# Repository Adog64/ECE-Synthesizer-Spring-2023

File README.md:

# ECE-Synthesizer-Spring-2023

Our project consists of a synthesizer that plays notes from C4 to B5 using buttons. The MSP430 provides square, triangle, and sawtooth waves. The audio will be comprised of a combination of these waves, which can be altered. The volume will be adjustable.

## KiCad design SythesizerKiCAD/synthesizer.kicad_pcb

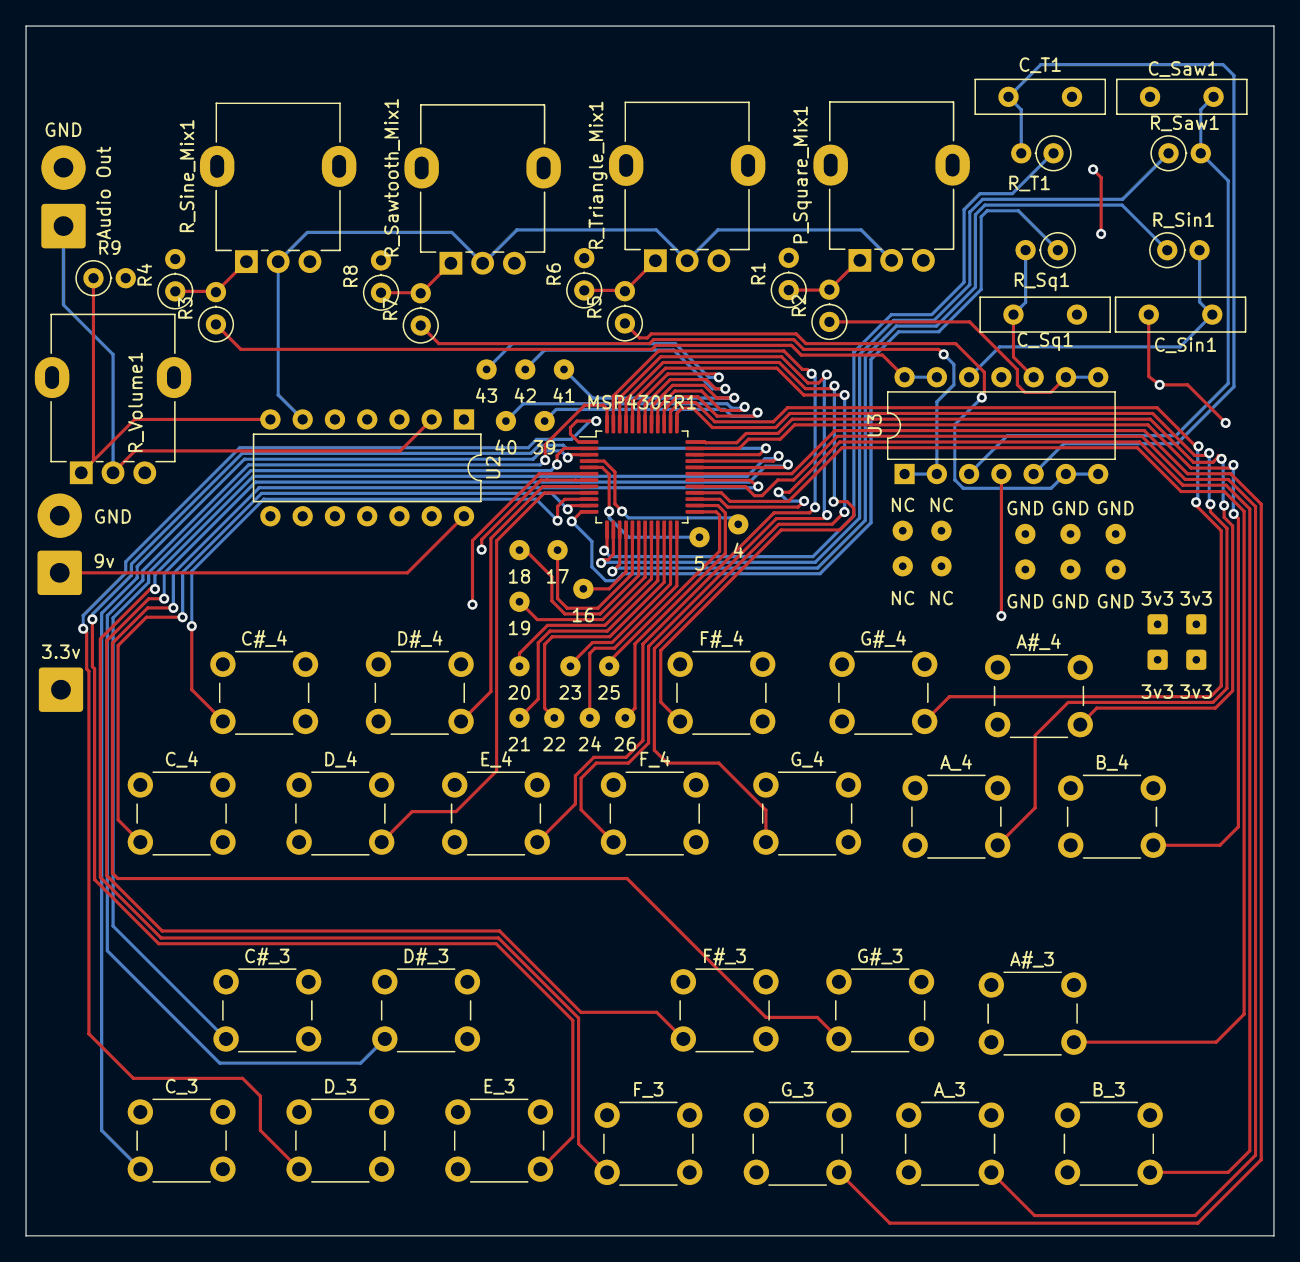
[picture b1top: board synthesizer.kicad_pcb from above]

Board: 2 copper layers, 98.2 x 95.2 mm, 86 parts (0 on the bottom side), 48 nets.

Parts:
3.3v, 9v: SolderWire-0.75sqmm_1x01_D1.25mm_OD3.5mm
3v3, 3v3#2, 3v3#3, 3v3#4, 4, 5, 16, 17, 18, 19, 20, 21, 22, 23, 24, 25, 26, 39, 40, 41, 42, 43: SolderWire-0.1sqmm_1x01_D0.4mm_OD1mm
A#_3, A#_4: SW_Push; SW_PUSH_6mm_H5mm
A_3, A_4: SW_Push; SW_PUSH_6mm_H5mm
Audio Out: SolderWire-0.75sqmm_1x01_D1.25mm_OD3.5mm
B_3, B_4: SW_Push; SW_PUSH_6mm_H5mm
C#_3, C#_4: SW_Push; SW_PUSH_6mm_H5mm
C_3, C_4: SW_Push; SW_PUSH_6mm_H5mm
C_Saw1: 1nF; C_Disc_D10.0mm_W2.5mm_P5.00mm
C_Sin1: 1nF; C_Disc_D10.0mm_W2.5mm_P5.00mm
C_Sq1: 1nF; C_Disc_D10.0mm_W2.5mm_P5.00mm
C_T1: 1nF; C_Disc_D10.0mm_W2.5mm_P5.00mm
D#_3, D#_4: SW_Push; SW_PUSH_6mm_H5mm
D_3, D_4: SW_Push; SW_PUSH_6mm_H5mm
E_3, E_4: SW_Push; SW_PUSH_6mm_H5mm
F#_3, F#_4: SW_Push; SW_PUSH_6mm_H5mm
F_3, F_4: SW_Push; SW_PUSH_6mm_H5mm
G#_3, G#_4: SW_Push; SW_PUSH_6mm_H5mm
GND: SolderWire-0.1sqmm_1x01_D0.4mm_OD1mm
GND#2, GND#3, GND#4, GND#6, GND#8: SolderWire-0.1sqmm_1x01_D0.4mm_OD1mm
GND#5, GND#7: SolderWire-0.75sqmm_1x01_D1.25mm_OD3.5mm
G_3, G_4: SW_Push; SW_PUSH_6mm_H5mm
MSP430FR1: LQFP-48_7x7mm_P0.5mm
NC: SolderWire-0.1sqmm_1x01_D0.4mm_OD1mm
NC#2, NC#3, NC#4: SolderWire-0.1sqmm_1x01_D0.4mm_OD1mm
P_Square_Mix1: R_Potentiometer_US; Potentiometer_Alpha_RD901F-40-00D_Single_Vertical
R1, R4, R6, R8, R9: 100k; R_Axial_DIN0207_L6.3mm_D2.5mm_P2.54mm_Vertical
R2, R3, R5, R7: 300k; R_Axial_DIN0207_L6.3mm_D2.5mm_P2.54mm_Vertical
R_Saw1: 8.2k; R_Axial_DIN0207_L6.3mm_D2.5mm_P2.54mm_Vertical
R_Sawtooth_Mix1: R_Potentiometer_US; Potentiometer_Alpha_RD901F-40-00D_Single_Vertical
R_Sin1: 8.2k; R_Axial_DIN0207_L6.3mm_D2.5mm_P2.54mm_Vertical
R_Sine_Mix1: R_Potentiometer_US; Potentiometer_Alpha_RD901F-40-00D_Single_Vertical
R_Sq1: 8.2k; R_Axial_DIN0207_L6.3mm_D2.5mm_P2.54mm_Vertical
R_T1: 8.2k; R_Axial_DIN0207_L6.3mm_D2.5mm_P2.54mm_Vertical
R_Triangle_Mix1: R_Potentiometer_US; Potentiometer_Alpha_RD901F-40-00D_Single_Vertical
R_Volume1: R_Potentiometer_US; Potentiometer_Alpha_RD901F-40-00D_Single_Vertical
U2: LM1877; DIP-14_W7.62mm
U3: LMC6484; DIP-14_W7.62mm

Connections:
/3v3: 3.3v.1, 3v3.1, 3v3#2.1, 3v3#3.1, 3v3#4.1, A#_3.1, A#_4.1, A_3.1, A_4.1, B_3.1, B_4.1, C#_3.1, C#_4.1, C_3.1, C_4.1, D#_3.1, D#_4.1, D_3.1, D_4.1, E_3.1, E_4.1, F#_3.1, F#_4.1, F_3.1, F_4.1, G#_3.1, G#_4.1, G_3.1, G_4.1, MSP430FR1.6 (DVCC), U3.4 (V+)
/9v: 9v.1, U2.14 (V+)
/Audio_Out: Audio Out.1, GND#5.1, R_Volume1.2, U2.2
/GND: C_Saw1.2, C_Sin1.2, C_Sq1.2, C_T1.2, GND.1, GND#2.1, GND#3.1, GND#4.1, GND#6.1, GND#7.1, GND#8.1, MSP430FR1.7 (DVSS), P_Square_Mix1.3, R1.2, R4.2, R6.2, R8.2, R9.2, R_Sawtooth_Mix1.3, R_Sine_Mix1.3, R_Triangle_Mix1.3, U2.3 (GND), U2.4 (GND), U2.5 (GND), U2.10 (GND), U2.11 (GND), U2.12 (GND), U3.11 (V-)
/Mixed: P_Square_Mix1.2, R_Sawtooth_Mix1.2, R_Sine_Mix1.2, R_Triangle_Mix1.2, U2.6 (+)
/P1.0: C_3.2, MSP430FR1.3 (P1.0/UCB0STE/SMCLK/COMP0.0/A0/Veref+)
/P1.1: C#_3.2, MSP430FR1.2 (P1.1/UCB0CLK/ACLK/OA0O/COMP0.1/A1)
/P1.2: D_3.2, MSP430FR1.1 (P1.2/UCB0SIMO/UCB0SDA/TB0TRG/OA0-/A2/Ve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)
/P1.3: D#_3.2, MSP430FR1.48 (1.3/UCB0SOMI/UCB0SCL/A3)
/P1.4: E_3.2, MSP430FR1.34 (P1.4/UCA0STE/TCK/A4)
/P1.5: F_3.2, MSP430FR1.33 (P1.5/UCA0CLK/TMS/A5)
/P1.6: F#_3.2, MSP430FR1.32 (P1.6/UCA0RXD/UCA0SOMI/TB0.1/TDI/TCLK/A6)
/P1.7: G_3.2, MSP430FR1.31 (P1.7/UCA0TXD/UCA0SIMO/TB0.2/TDO/A7/VREF+)
/P2.0: G#_3.2, MSP430FR1.30 (P2.0/TB1.1/COMP0.O)
/P2.1: A_3.2, MSP430FR1.29 (P2.1/TB1.2/COMP1.O)
/P2.2: A#_3.2, MSP430FR1.28 (P2.2/TB1CLK)
/P2.3: B_3.2, MSP430FR1.27 (P2.3/TB1TRG)
/P2.4: C_4.2, MSP430FR1.11 (P2.4/COMP1.1)
/P2.5: C#_4.2, MSP430FR1.10 (P2.5/COMP1.0)
/P2.6: D_4.2, MSP430FR1.9 (P2.6/MCLK/XOUT)
/P2.7: D#_4.2, MSP430FR1.8 (P2.7/TB0CLK/XIN)
/P3.0: E_4.2, MSP430FR1.47 (P3.0/MCLK)
/P3.1: F_4.2, MSP430FR1.46 (P3.1)
/P3.2: F#_4.2, MSP430FR1.45 (P3.2)
/P3.3: G_4.2, MSP430FR1.44 (P3.3)
/P3.4: G#_4.2, MSP430FR1.38 (P3.4/SMCLK)
/P3.5: A_4.2, MSP430FR1.37 (P3.5)
/P3.6: A#_4.2, MSP430FR1.36 (P3.6)
/P3.7: B_4.2, MSP430FR1.35 (P3.7)
/Sawtooth_Analog: C_Saw1.1, R_Saw1.2, U3.3 (+)
/Sawtooth_Divided: R7.2, R8.1, R_Sawtooth_Mix1.1
/Sawtooth_Isolated: R7.1, U3.1, U3.2 (-)
/Sawtooth_PWM: MSP430FR1.14 (P4.5/UCB1CLK), R_Saw1.1
/Sine_Analog: C_Sin1.1, R_Sin1.2, U3.12 (+)
/Sine_Divided: R3.2, R4.1, R_Sine_Mix1.1
/Sine_Isolated: R3.1, U3.13 (-), U3.14
/Sine_PWM: MSP430FR1.15 (P4.4/UCB1STE), R_Sin1.1
/Square_Analog: C_Sq1.1, R_Sq1.2, U3.10 (+)
/Square_Divided: P_Square_Mix1.1, R1.1, R2.2
/Square_Isolated: R2.1, U3.8, U3.9 (-)
/Square_PWM: MSP430FR1.12 (P4.7/UCB1SOMI/UCB1SCL), R_Sq1.1
/Triangle_Analog: C_T1.1, R_T1.2, U3.5 (+)
/Triangle_Divided: R5.2, R6.1, R_Triangle_Mix1.1
/Triangle_Isolated: R5.1, U3.6 (-), U3.7
/Triangle_PWM: MSP430FR1.13 (P4.6/UCB1SIMO/UCB1SDA), R_T1.1
/UART_MSP_RX: 24.1, MSP430FR1.24 (P4.2/UCA1RXD/UCA1SOMI/UCA1RXD)
/UART_MSP_TX: 23.1, MSP430FR1.23 (P4.3/UCA1TXD/UCA1SIMO/UCA1TXD)
unnamed: R9.1, R_Volume1.1, U2.7 (-)

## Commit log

2023-03-23 Added abstract to the project overview
2023-03-23 Organized files into folders
2023-03-27 initGPIO
2023-04-04 Mostly done with PCB.
2023-04-04 Lowpass filters and isolators
2023-04-05 Volume, audio out, power in
2023-04-05 Fixed ground issue
2023-04-06 Removed NINA, breakouts for MSP, extra pads
2023-04-06 Generated Gerber Files and Drill Files
2023-04-13 Frequencies and timer periods
2023-04-26 Some MCU code updates
2023-05-01 Python PWM generator
2023-05-01 PWM Simulations
2023-05-01 First iter PWM signal outputs
2023-05-03 MSP test code & filter sim
2023-05-03 Hopefully triangle waves?
2023-05-04 Wave testing: devolvment into chaos
2023-05-07 Final code and report
